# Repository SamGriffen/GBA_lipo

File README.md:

# GBA_lipo
LiPo mod for gameboy advance

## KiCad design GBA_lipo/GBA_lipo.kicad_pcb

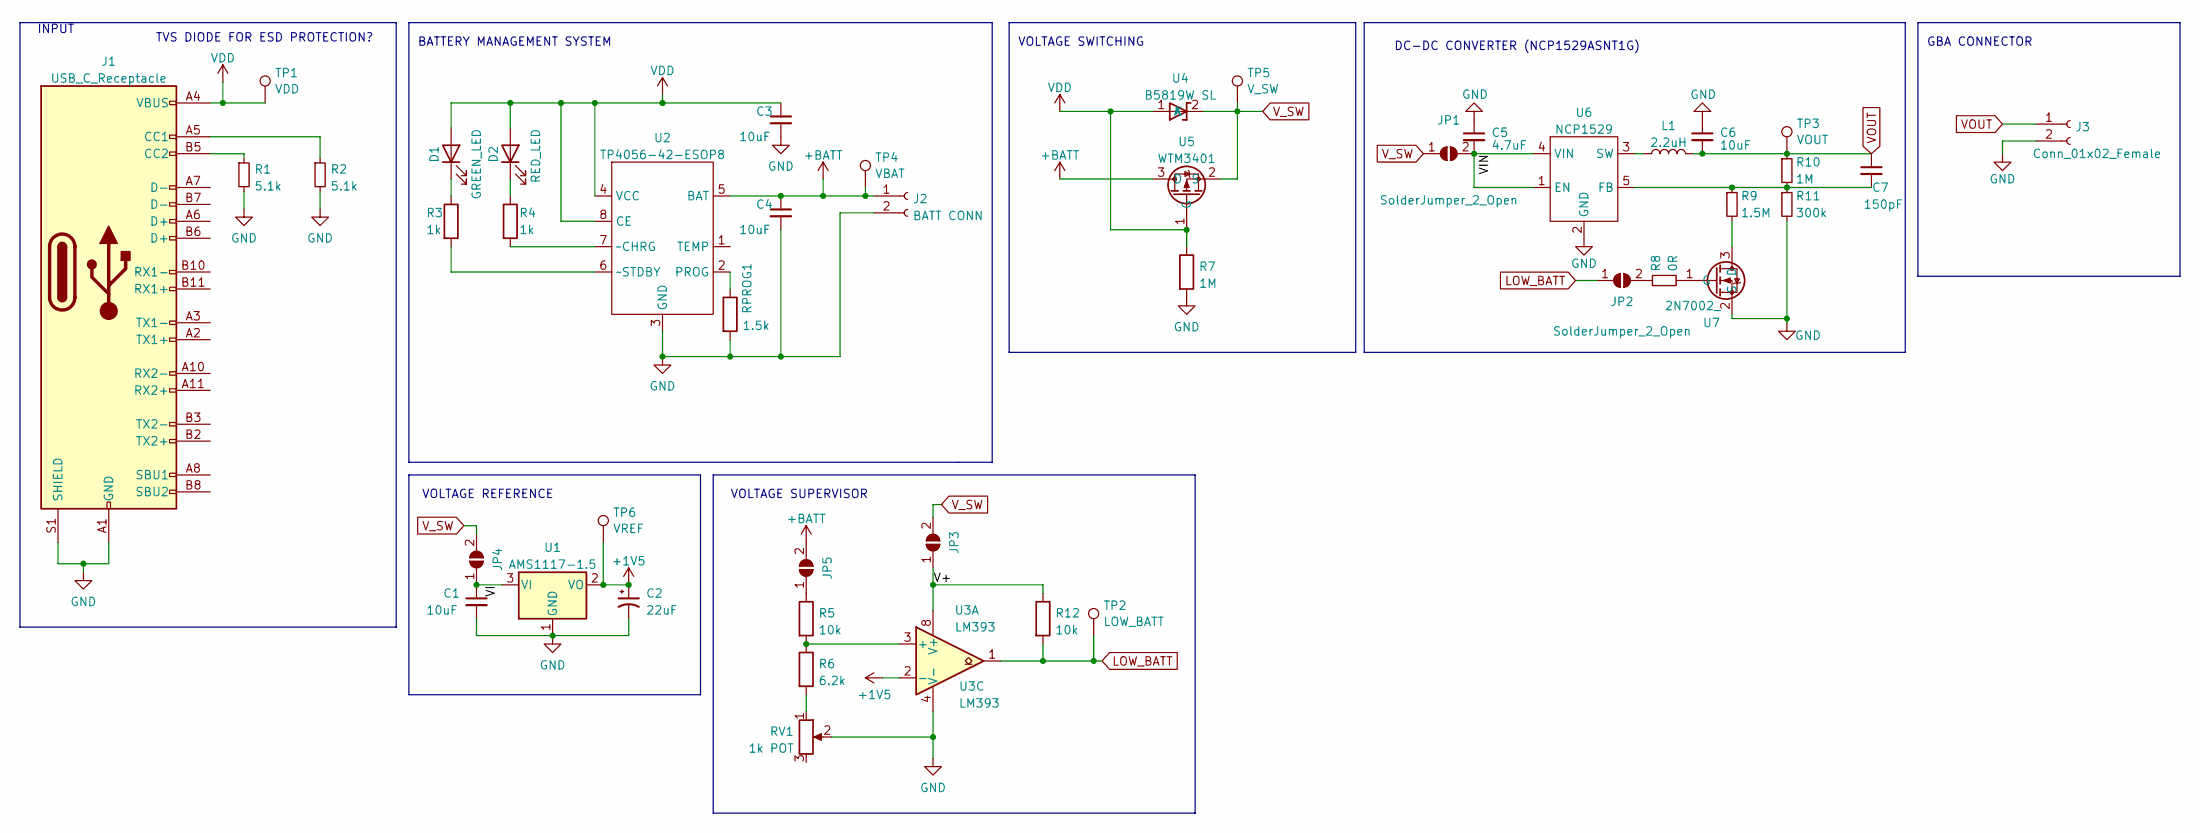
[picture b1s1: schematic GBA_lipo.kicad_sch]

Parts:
C1, C3, C4: 10uF; C_0603_1608Metric; JLCPCB Part # C19702
C2: 22uF; C_0603_1608Metric; JLCPCB Part # C59461
C5: 4.7uF; C_0603_1608Metric; JLC_Part# C19666
C6: 10uF; C_0603_1608Metric; JLC_Part# C19702
C7: 150pF; C_0603_1608Metric; JLC_Part# C1594
D1: GREEN_LED; LED_0603_1608Metric
D2: RED_LED; LED_0603_1608Metric
J1: USB_C_Receptacle; USB_C_Receptacle_HRO_TYPE-C-31-M-12; JLCPCB Part # C709357
J2: BATT CONN; PinHeader_1x02_P1.27mm_Vertical
J3: Conn_01x02_Female; PinHeader_1x02_P1.27mm_Vertical
JP1, JP2, JP3, JP4, JP5: SolderJumper_2_Open; SolderJumper-2_P1.3mm_Open_Pad1.0x1.5mm
L1: 2.2uH; L_1206_3216Metric_Pad1.42x1.75mm_HandSolder; JLC_Part# C1043
R1, R2: 5.1k; R_0603_1608Metric; JLCPCB Part # C23186
R3, R4: 1k; R_0603_1608Metric; JLCPCB Part # C21190
R5: 10k; R_0603_1608Metric; JLCPCB Part # C25197
R6: 6.2k; R_0603_1608Metric; JLCPCB Part # C4260
R7, R10: 1M; R_0603_1608Metric; JLC_Part# C22935
R8: 0R; R_0603_1608Metric
R9: 1.5M; R_0603_1608Metric; JLC_Part# C4172
R11: 300k; R_0603_1608Metric; JLC_Part# C23024
R12: 10k; R_0603_1608Metric; JLCPCB Part # C4260
RPROG1: 1.5k; R_0603_1608Metric; JLCPCB Part # C22843
RV1: 1k POT; Potentiometer_Bourns_TC33X_Vertical; JLC_Part# NOT FROM JLC
TP1: VDD; TestPoint_Pad_1.0x1.0mm
TP2: LOW_BATT; TestPoint_Pad_1.0x1.0mm
TP3: VOUT; TestPoint_Pad_1.0x1.0mm
TP4: VBAT; TestPoint_Pad_1.0x1.0mm
TP5: V_SW; TestPoint_Pad_1.0x1.0mm
TP6: VREF; TestPoint_Pad_1.0x1.0mm
U1: AMS1117-1.5; SOT-223-3_TabPin2; JLCPCB Part # NOT FROM JLC
U2: TP4056-42-ESOP8; SOIC-8-1EP_3.9x4.9mm_P1.27mm_EP2.29x3mm; JLCPCB Part # C16581
U3: LM393; SOIC-8_3.9x4.9mm_P1.27mm; JLCPCB Part # C7955
U4: B5819W SL; D_SOD-123; JLCPCB Part # C8598
U5: WTM3401; SOT-23; JLC_Part# C2847494
U6: NCP1529; SOT-23-5_HandSoldering; JLC_Part# NOT FROM JLC
U7: 2N7002_; SOT-23; JLC_Part# C8545

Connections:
+1V5: C2.1, TP6.1, U1.2 (VO), U3.2 (-)
+BATT: C4.1, J2.1, JP5.2 (B), TP4.1, U2.5 (BAT), U5.3 (D)
/V+: JP3.1 (A), R12.1, U3.8 (V+)
/VI: C1.1, JP4.1 (A), U1.3 (VI)
/VIN: C5.2, JP1.2 (B), U6.1 (EN), U6.4 (VIN)
GND: C1.2, C2.2, C3.2, C4.2, C5.1, C6.1, J1.A1 (GND), J1.A12 (GND), J1.B1 (GND), J1.B12 (GND), J1.S1 (SHIELD), J2.2, J3.2, R1.2, R2.2, R7.2, R11.2, RPROG1.2, RV1.2, U1.1 (GND), U2.3 (GND), U3.4 (V-), U6.2 (GND), U7.2 (S)
LOW_BATT: JP2.1 (A), R12.2, TP2.1, U3.1
unnamed: D1.1 (K), R3.1
unnamed: D2.1 (K), R4.1
unnamed: J1.A5 (CC1), R2.1
unnamed: J1.B5 (CC2), R1.1
unnamed: JP2.2 (B), R8.1
unnamed: JP5.1 (A), R5.1
unnamed: R6.2, RV1.1
unnamed: RPROG1.1, U2.2 (PROG)
unnamed: R4.2, U2.7 (~CHRG)
unnamed: R3.2, U2.6 (~STDBY)
unnamed: R5.2, R6.1, U3.3 (+)
unnamed: C7.2, R9.1, R10.2, R11.1, U6.5 (FB)
unnamed: L1.1, U6.3 (SW)
unnamed: R9.2, U7.3 (D)
unnamed: R8.2, U7.1 (G)
VDD: C3.1, D1.2 (A), D2.2 (A), J1.A4 (VBUS), J1.A9 (VBUS), J1.B4 (VBUS), J1.B9 (VBUS), R7.1, TP1.1, U2.4 (VCC), U2.8 (CE), U4.1 (A), U5.1 (G)
VOUT: C6.2, C7.1, J3.1, L1.2, R10.1, TP3.1
V_SW: JP1.1 (A), JP3.2 (B), JP4.2 (B), TP5.1, U4.2 (K), U5.2 (S)

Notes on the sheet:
INPUT
TVS DIODE FOR ESD PROTECTION?
GBA CONNECTOR
VOLTAGE REFERENCE
VOLTAGE SUPERVISOR
BATTERY MANAGEMENT SYSTEM
VOLTAGE SWITCHING
DC-DC CONVERTER (NCP1529ASNT1G)

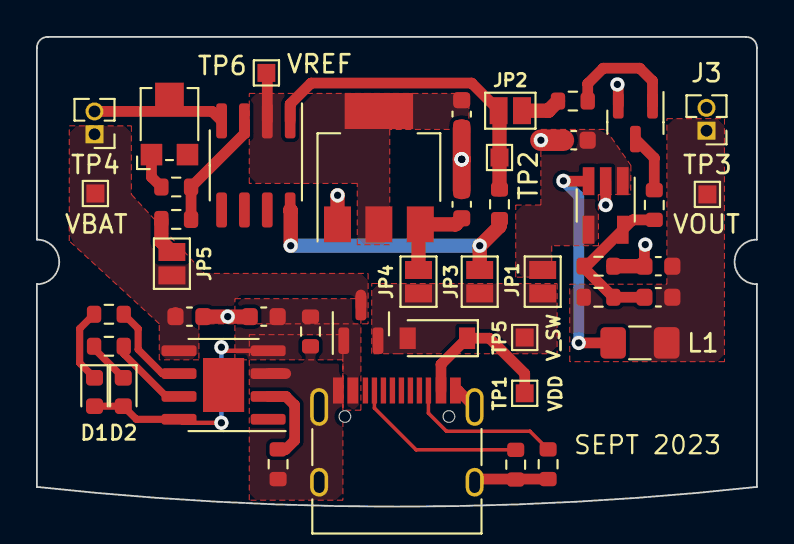
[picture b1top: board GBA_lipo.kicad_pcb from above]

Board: 2 copper layers, 40.0 x 26.1 mm, 45 parts (0 on the bottom side), 25 nets.

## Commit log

2022-07-29 Schematic finished
2022-07-30 Layout work
2023-09-04 Fab Version 1.0
